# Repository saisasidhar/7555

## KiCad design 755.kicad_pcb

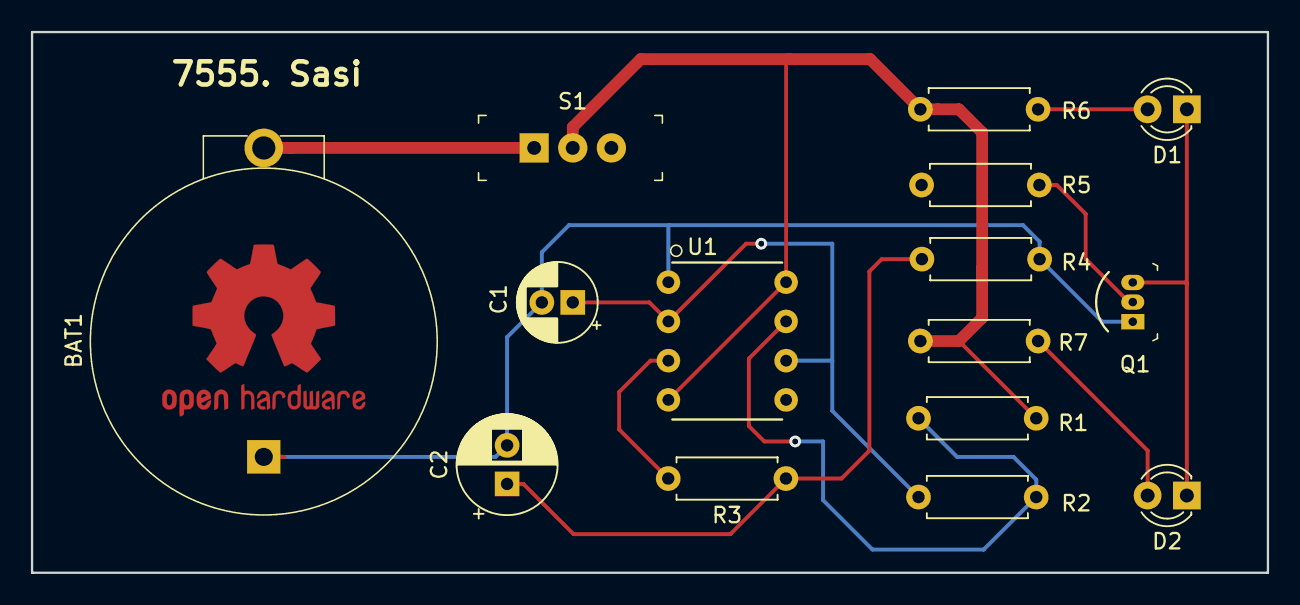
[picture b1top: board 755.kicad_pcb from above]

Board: 2 copper layers, 80.0 x 35.0 mm, 15 parts (0 on the bottom side), 11 nets.

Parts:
BAT1: BS-7; Battery_Holder_Coin_2032_BS-7
C1: 10u; CP_Radial_D5.0mm_P2.00mm
C2: 100u; CP_Radial_D6.3mm_P2.50mm
D1, D2: RED; LED_D3.0mm
Q1: 2N3904; TO-92-3
R1: 22k; R_Axial_DIN0207_L6.3mm_D2.5mm_P7.62mm_Horizontal
R2: 330k; R_Axial_DIN0207_L6.3mm_D2.5mm_P7.62mm_Horizontal
R3: 22K; R_Axial_DIN0207_L6.3mm_D2.5mm_P7.62mm_Horizontal
R4: 100k; R_Axial_DIN0207_L6.3mm_D2.5mm_P7.62mm_Horizontal
R5: 10k; R_Axial_DIN0207_L6.3mm_D2.5mm_P7.62mm_Horizontal
R6, R7: 100; R_Axial_DIN0207_L6.3mm_D2.5mm_P7.62mm_Horizontal
S1: EG1218; Switch_Slide_11.6x4mm_EG1218
U1: 7555; ICM755-PDIP

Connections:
GND: BAT1.Neg, C1.2, C2.2, Q1.1, R4.2, U1.1
unnamed: BAT1.Pos, S1.1
unnamed: C1.1, R2.2, U1.2, U1.6
unnamed: C2.1, R3.1, R4.1, R5.2
unnamed: D1.1, D2.1, Q1.3
unnamed: D1.2, R6.2
unnamed: D2.2, R7.2
unnamed: Q1.2, R5.1
unnamed: R1.2, R2.1, U1.7
unnamed: R3.2, U1.3
VCC: R1.1, R6.1, R7.1, S1.2, U1.4, U1.8
